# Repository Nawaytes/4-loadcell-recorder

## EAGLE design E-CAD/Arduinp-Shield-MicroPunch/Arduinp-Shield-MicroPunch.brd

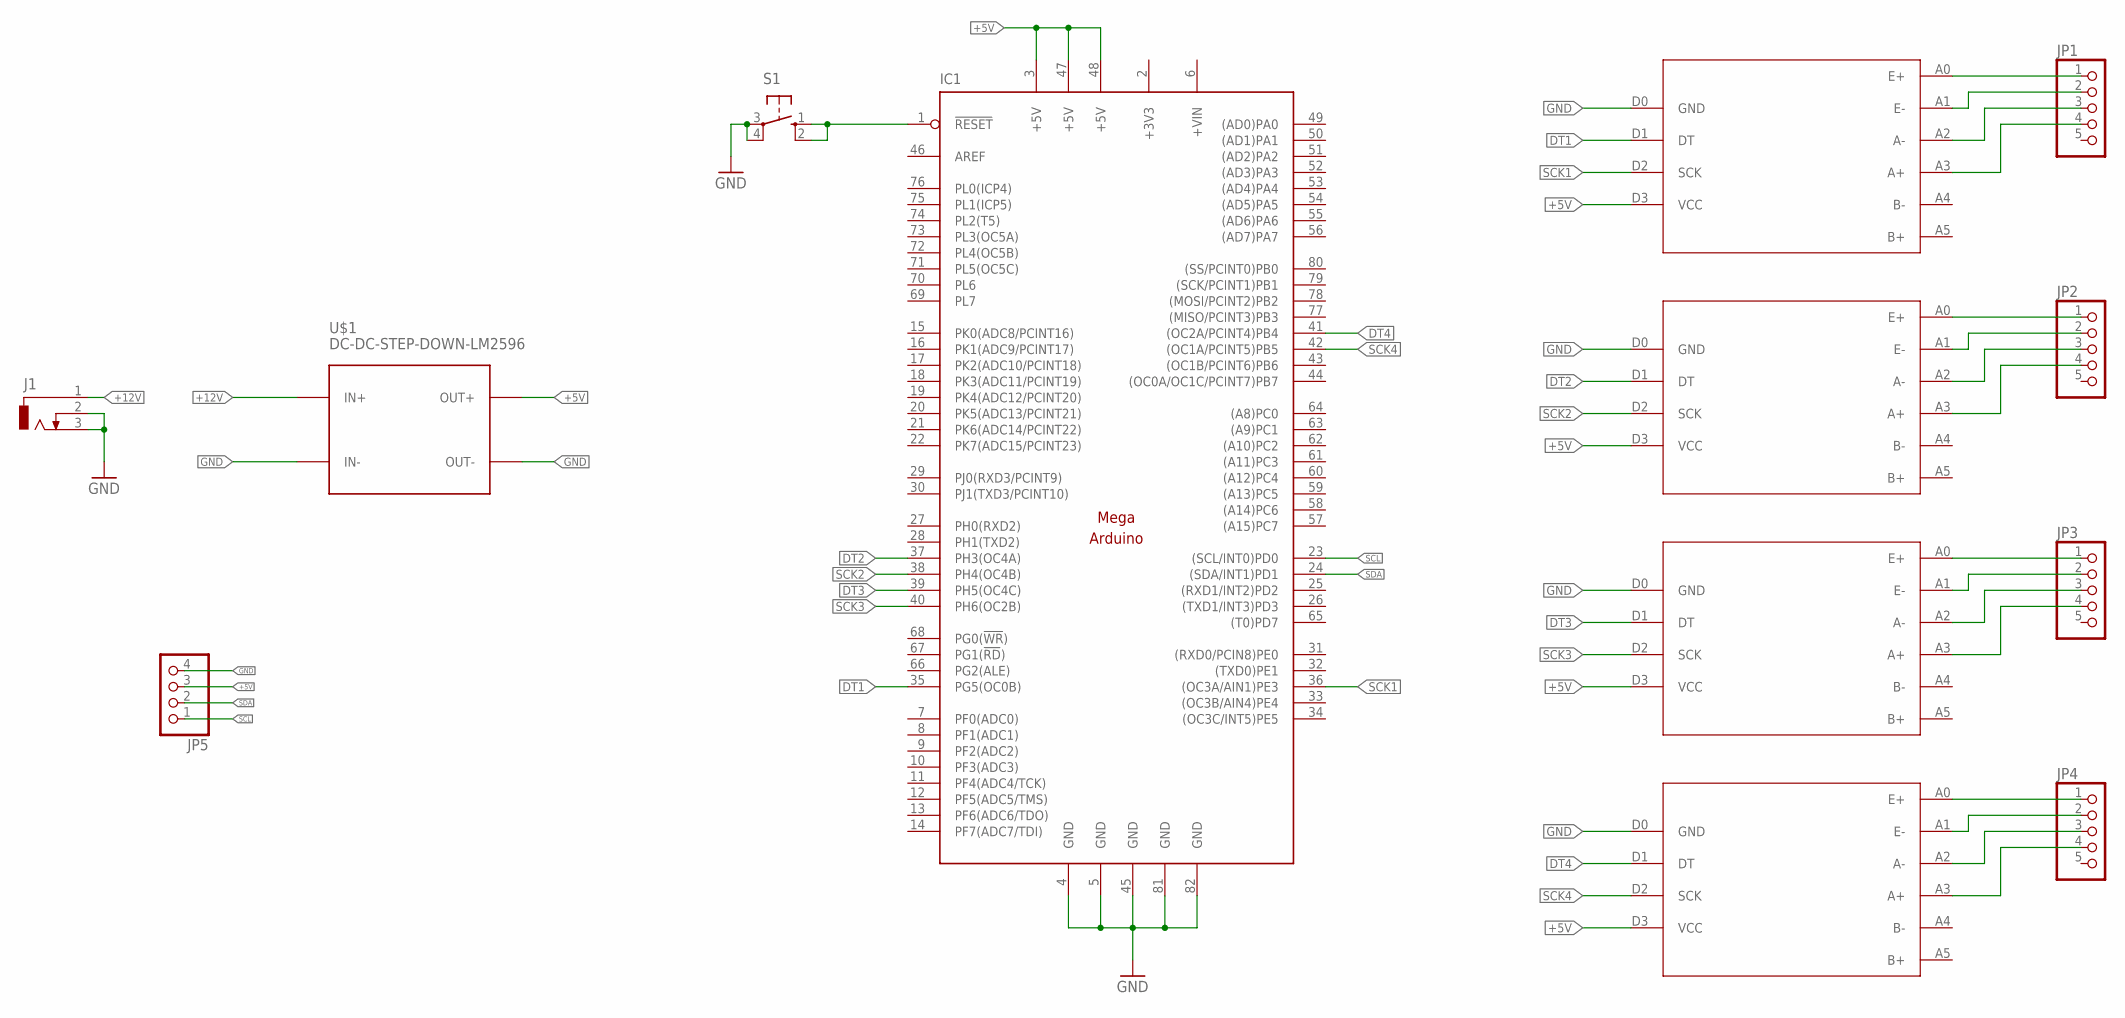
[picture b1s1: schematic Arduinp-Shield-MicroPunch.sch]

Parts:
IC1: MEGAARDUINO_11; MEGA_ARDUINO_1
J1: DCJ0303
JP1, JP2, JP3, JP4: PINHD-1X5; 1X05
JP5: PINHD-1X4; 1X04
S1: 10-XX; B3F-10XX
SM1, SM2, SM3, SM4: HX711
U$1: DC-DC-STEP-DOWN-LM2596

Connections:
+3V3: IC1.2 (+3V3)
+5V: IC1.3 (+5V), IC1.47 (+5V), IC1.48 (+5V), JP5.3, SM1.D3 (VCC), SM2.D3 (VCC), SM3.D3 (VCC), SM4.D3 (VCC), U$1.OUT+
+12V: J1.1, U$1.IN+
+VIN: IC1.6 (+VIN)
DT1: IC1.35 (PG5(OC0B)), SM1.D1 (DT)
DT2: IC1.37 (PH3(OC4A)), SM2.D1 (DT)
DT3: IC1.39 (PH5(OC4C)), SM3.D1 (DT)
DT4: IC1.41 ((OC2A/PCINT4)PB4), SM4.D1 (DT)
GND: IC1.4 (GND), IC1.5 (GND), IC1.45 (GND), IC1.81 (GND), IC1.82 (GND), J1.2, J1.3, JP5.4, S1.3, S1.4 (P1), SM1.D0 (GND), SM2.D0 (GND), SM3.D0 (GND), SM4.D0 (GND), U$1.IN-, U$1.OUT-
unnamed: IC1.1 (!RESET), S1.1 (S), S1.2 (S1)
unnamed: JP4.1, SM4.A0 (E+)
unnamed: JP4.2, SM4.A1 (E-)
unnamed: JP4.3, SM4.A2 (A-)
unnamed: JP4.4, SM4.A3 (A+)
unnamed: JP3.1, SM3.A0 (E+)
unnamed: JP3.2, SM3.A1 (E-)
unnamed: JP3.3, SM3.A2 (A-)
unnamed: JP3.4, SM3.A3 (A+)
unnamed: JP2.1, SM2.A0 (E+)
unnamed: JP2.2, SM2.A1 (E-)
unnamed: JP2.3, SM2.A2 (A-)
unnamed: JP2.4, SM2.A3 (A+)
unnamed: JP1.1, SM1.A0 (E+)
unnamed: JP1.2, SM1.A1 (E-)
unnamed: JP1.3, SM1.A2 (A-)
unnamed: JP1.4, SM1.A3 (A+)
SCK1: IC1.36 ((OC3A/AIN1)PE3), SM1.D2 (SCK)
SCK2: IC1.38 (PH4(OC4B)), SM2.D2 (SCK)
SCK3: IC1.40 (PH6(OC2B)), SM3.D2 (SCK)
SCK4: IC1.42 ((OC1A/PCINT5)PB5), SM4.D2 (SCK)
SCL: IC1.23 ((SCL/INT0)PD0), JP5.1
SDA: IC1.24 ((SDA/INT1)PD1), JP5.2

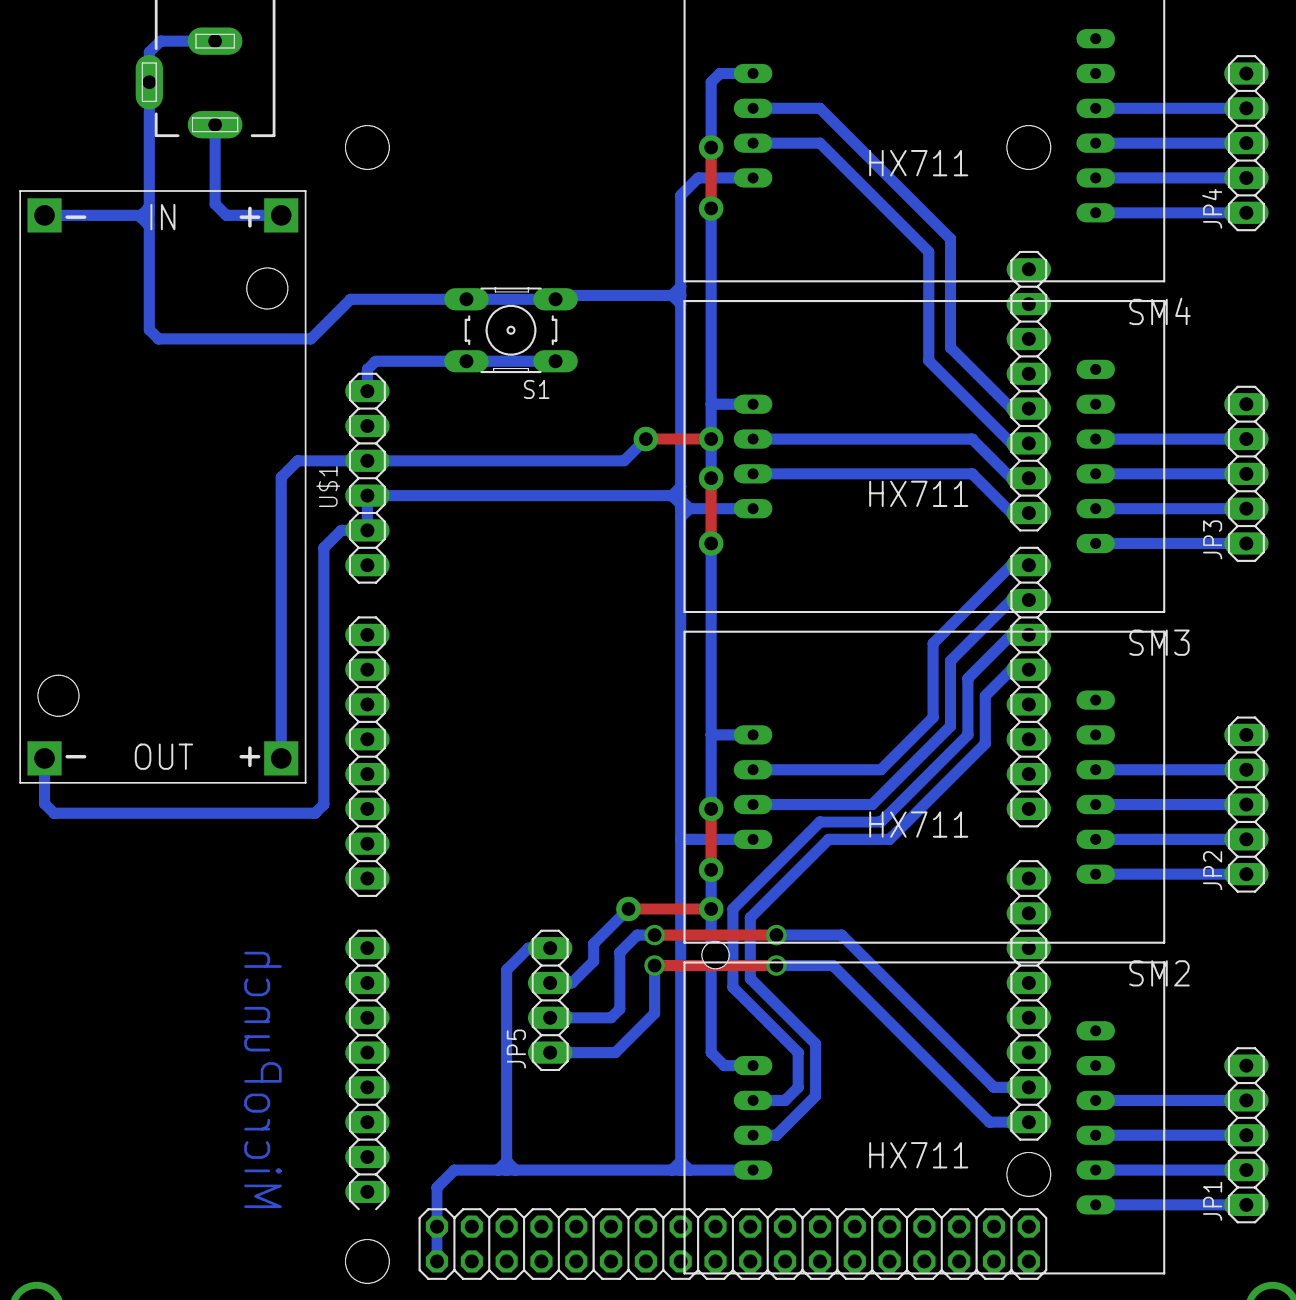
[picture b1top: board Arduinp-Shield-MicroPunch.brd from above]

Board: 2 copper layers, 13 parts (0 on the bottom side), 30 nets.

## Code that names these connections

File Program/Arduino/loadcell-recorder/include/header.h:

#define DT1  4
#define SCK1 5
#define DT2  6
#define SCK2 7
#define DT3  8
#define SCK3 9
#define DT4  10
#define SCK4 11

#define SENDALL 200
#define CALIBRATE 201
#define RECORD 202
#define PAUSE 203
#define SENDSUM 203

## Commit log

2020-12-11 base ECAD
2020-12-11 base arduino program
2020-12-11 base processing
2020-12-11 add HX711 library
2020-12-18 simple design
2020-12-18 EEPROM master
2020-12-19 base gui
2021-03-08 update new
2021-03-15 final

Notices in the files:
parts and their libraries:
diy-modules: Released under the Creative Commons Attribution 4.0 International License: http://creativecommons.org/licenses/by/4.0
